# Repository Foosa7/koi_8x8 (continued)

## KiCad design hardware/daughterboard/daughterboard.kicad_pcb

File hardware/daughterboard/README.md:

# Daughterboard — 8-channel analog board

The analog front-end board for Koi 8×8. Eight of these plug into one
[motherboard](../motherboard/) over a PCIe-x4 card-edge connector, giving the
system 8 boards × 8 channels = 64 independent current sources with voltage
readback. Formerly codenamed `OuttaQontrol`/`OuttaControl`.

| Top | Bottom |
| --- | --- |
|  |  |

Same top view with an alpha background, for dropping onto slides or into the
paper's figures:

## What's on it

| Ref | Part | Function |
| --- | --- | --- |
| U0–U7 | XTR200 (WSON-10) | Precision current-source front end, one per channel |
| U20 | DAC80508Z (WQFN-16) | 16-bit, 8-channel DAC — sets the 8 channel currents |
| U11 | AD7193 (TSSOP-28) | 24-bit ΔΣ ADC — reads back the 8 channel voltages |
| U10 | REF5030 (SOIC-8) | 3.0 V precision reference, shared by the DAC and ADC on this board |
| U8 | SN74LV165A (TSSOP-16) | Parallel-load 8-bit shift register |
| U9 | AT21CS01 | 1-Wire EEPROM (board ID/config) — new in this revision |
| R19–R26 | 4.7 kΩ 0.1 % | Per-channel sense resistors |
| R1–R4, R9–R12, R17 / R5–R8, R13–R16 | 100 kΩ / 20 kΩ 0.1 % | 6:1 sense divider (top/bottom) — firmware reads the raw ADC-pin voltage and the host applies ×6 to get true heater voltage |
| J1 | Custom PCIe-x4 card-edge | Connector into the motherboard slot |

Full pricing and part numbers: [`../../master_bom.csv`](../../master_bom.csv).

## Files

| File | What it is |
| --- | --- |
| `daughterboard.kicad_pro` / `.kicad_sch` / `.kicad_pcb` | The KiCad project (current revision) |
| `Schematics/daughterboard.pdf` | Exported schematic |
| `bom/ibom.html` | Interactive HTML BOM (open in a browser) |
| `production/` | Fab outputs — gerbers, BOM, positions, netlist |
| `daughterboard*.png` | Board views above, regenerated with `kicad-cli pcb render` |
| `version 1/` | The prior board revision (pre-EEPROM), kept for reference, incl. its own PDN sim results |
| `padne_out_v3/`, `results_v3/` | Power-delivery-network (PDN) simulation outputs for this revision — current-density and IR-drop maps |

Photorealistic Cycles renders (`daughterboard_render*.png`) are produced by the
pipeline in [`../render/`](../render/) — not generated yet.

See **[`CLAUDE.md`](CLAUDE.md)** for the full development-facing breakdown of
these files, the netlist/revision history, and the padne PDN simulation
workflow in detail.

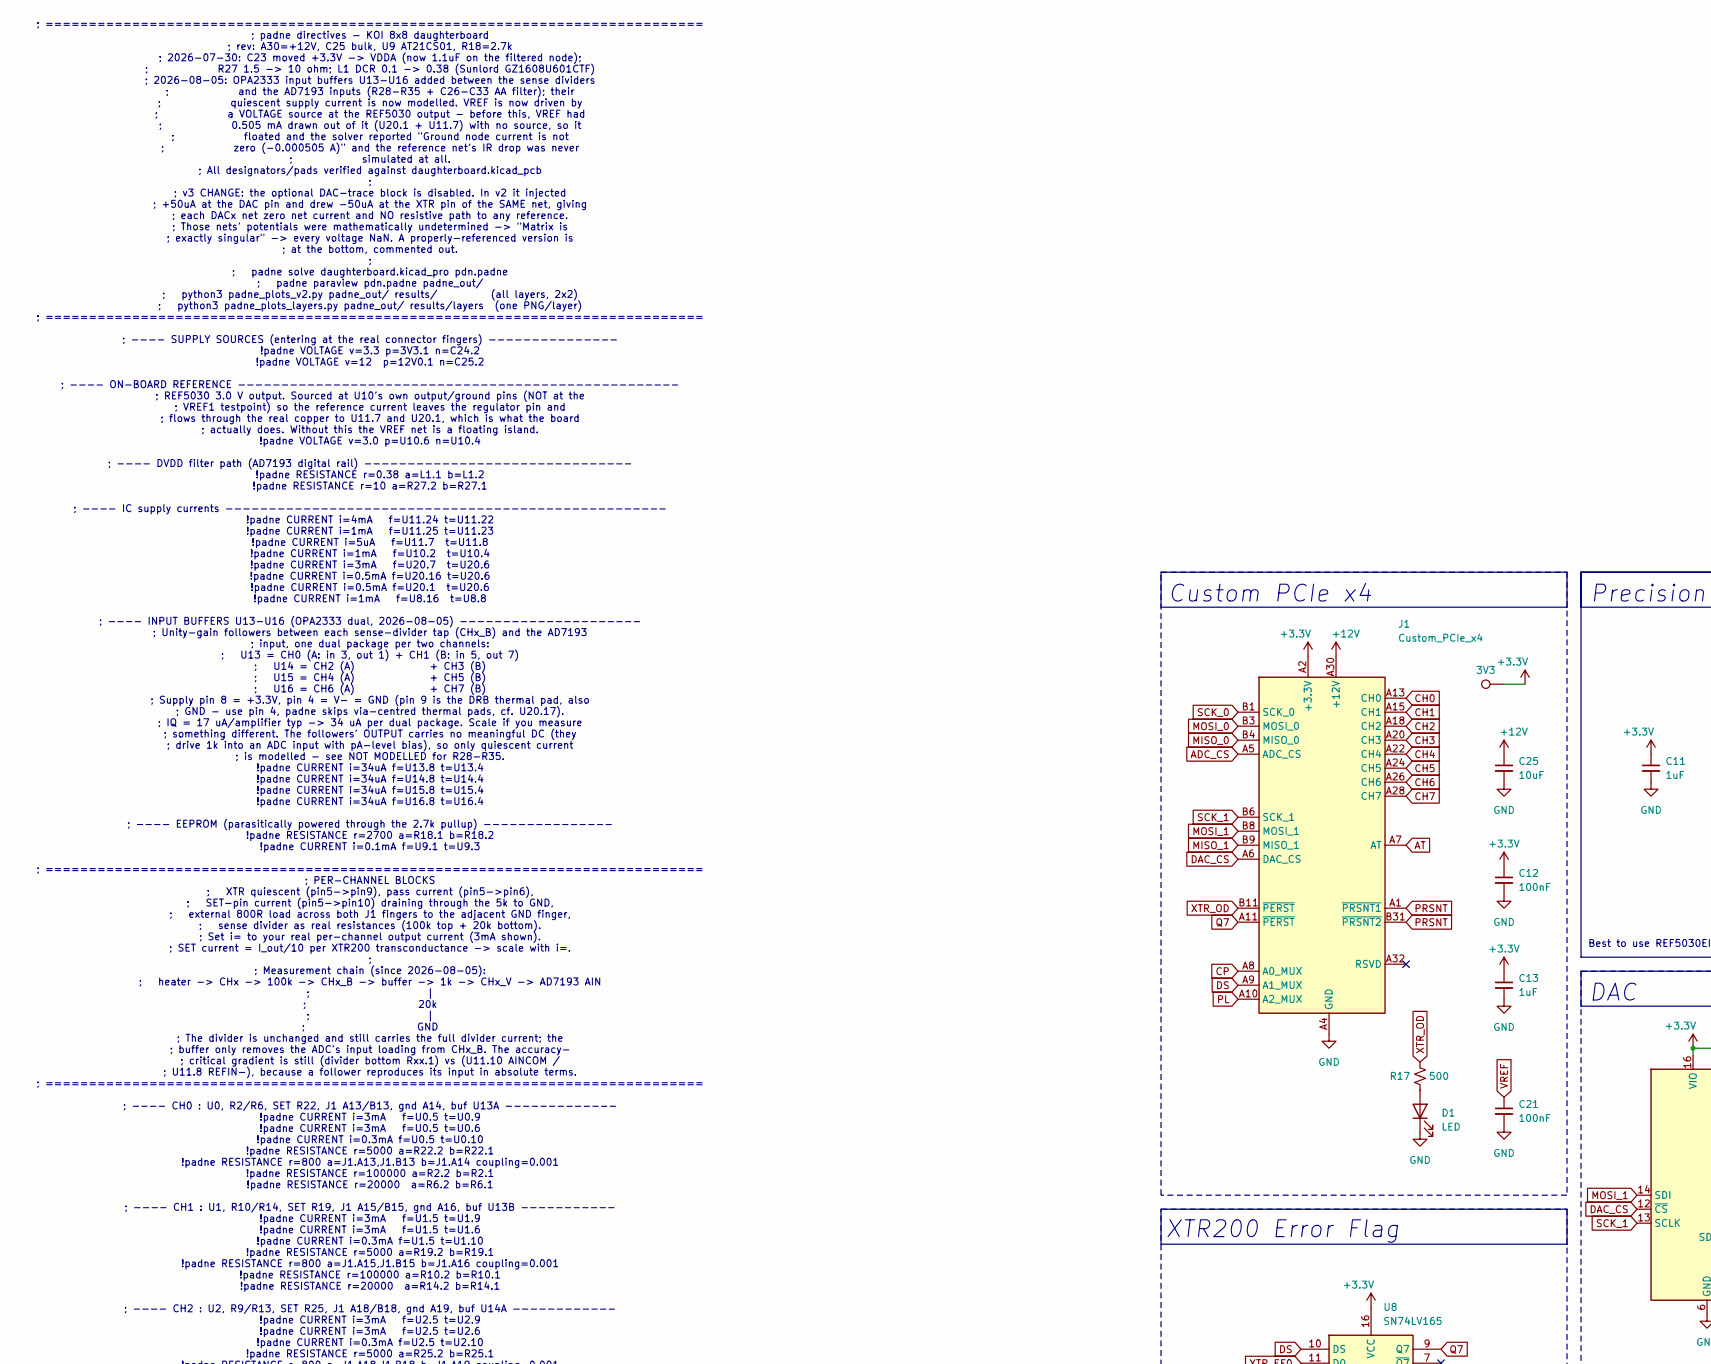
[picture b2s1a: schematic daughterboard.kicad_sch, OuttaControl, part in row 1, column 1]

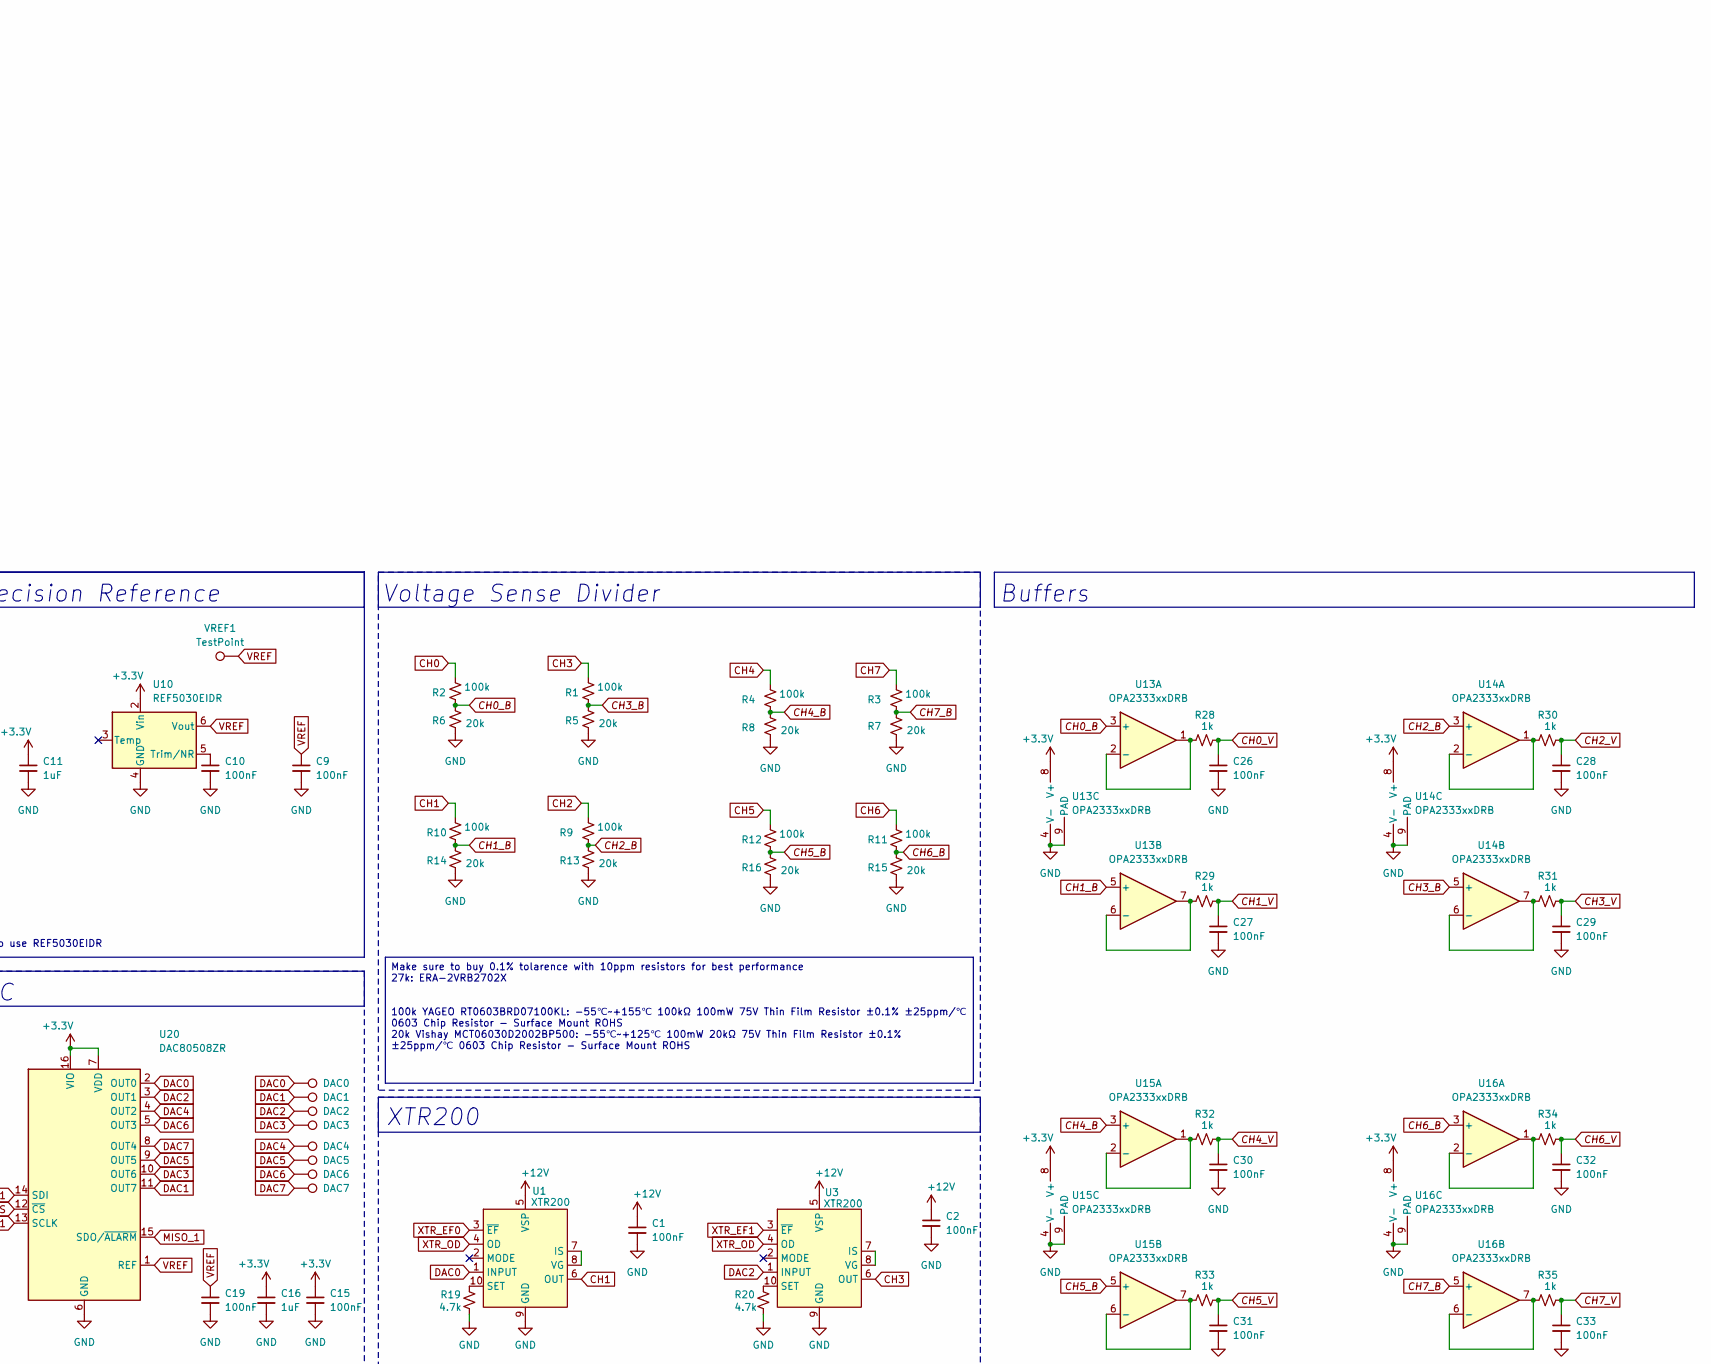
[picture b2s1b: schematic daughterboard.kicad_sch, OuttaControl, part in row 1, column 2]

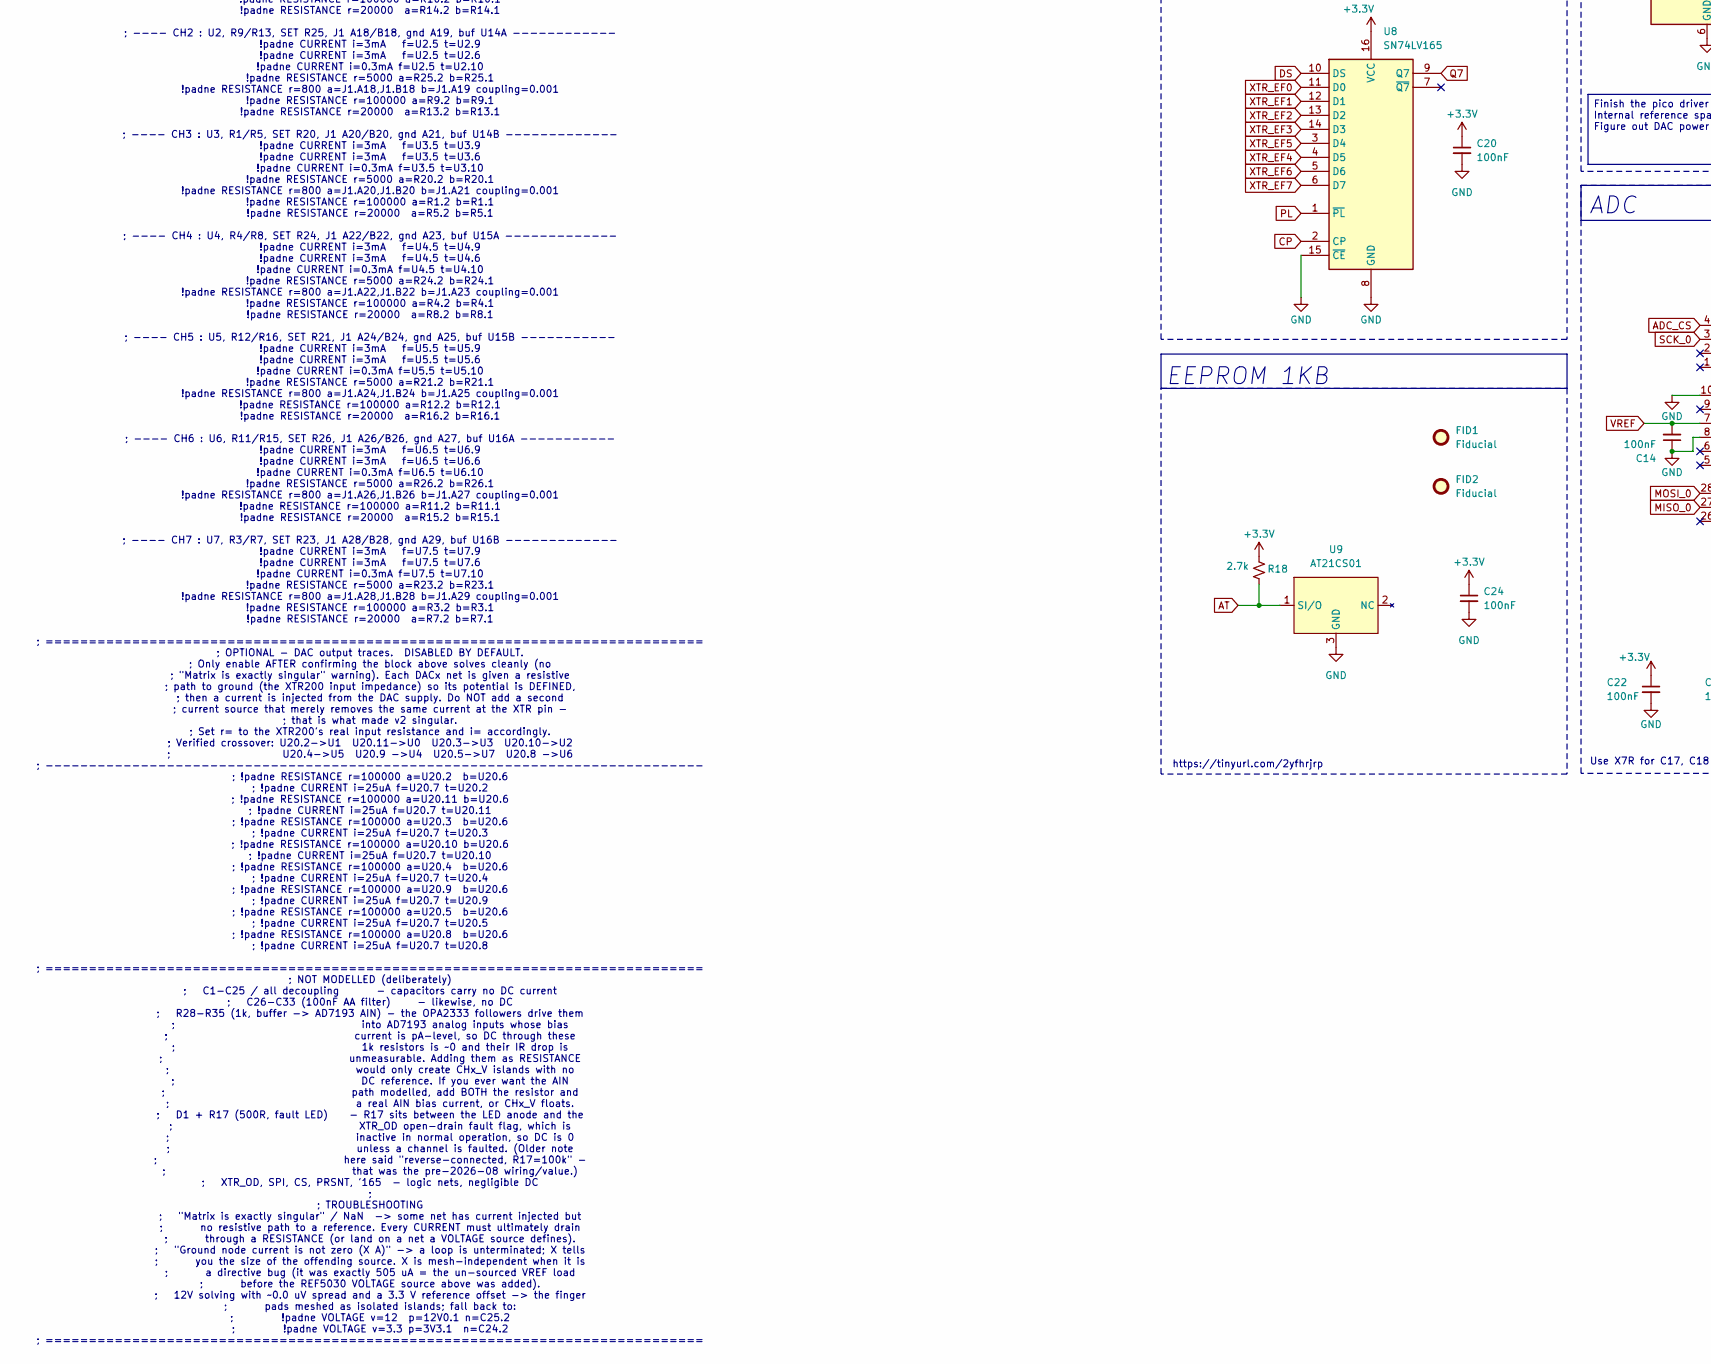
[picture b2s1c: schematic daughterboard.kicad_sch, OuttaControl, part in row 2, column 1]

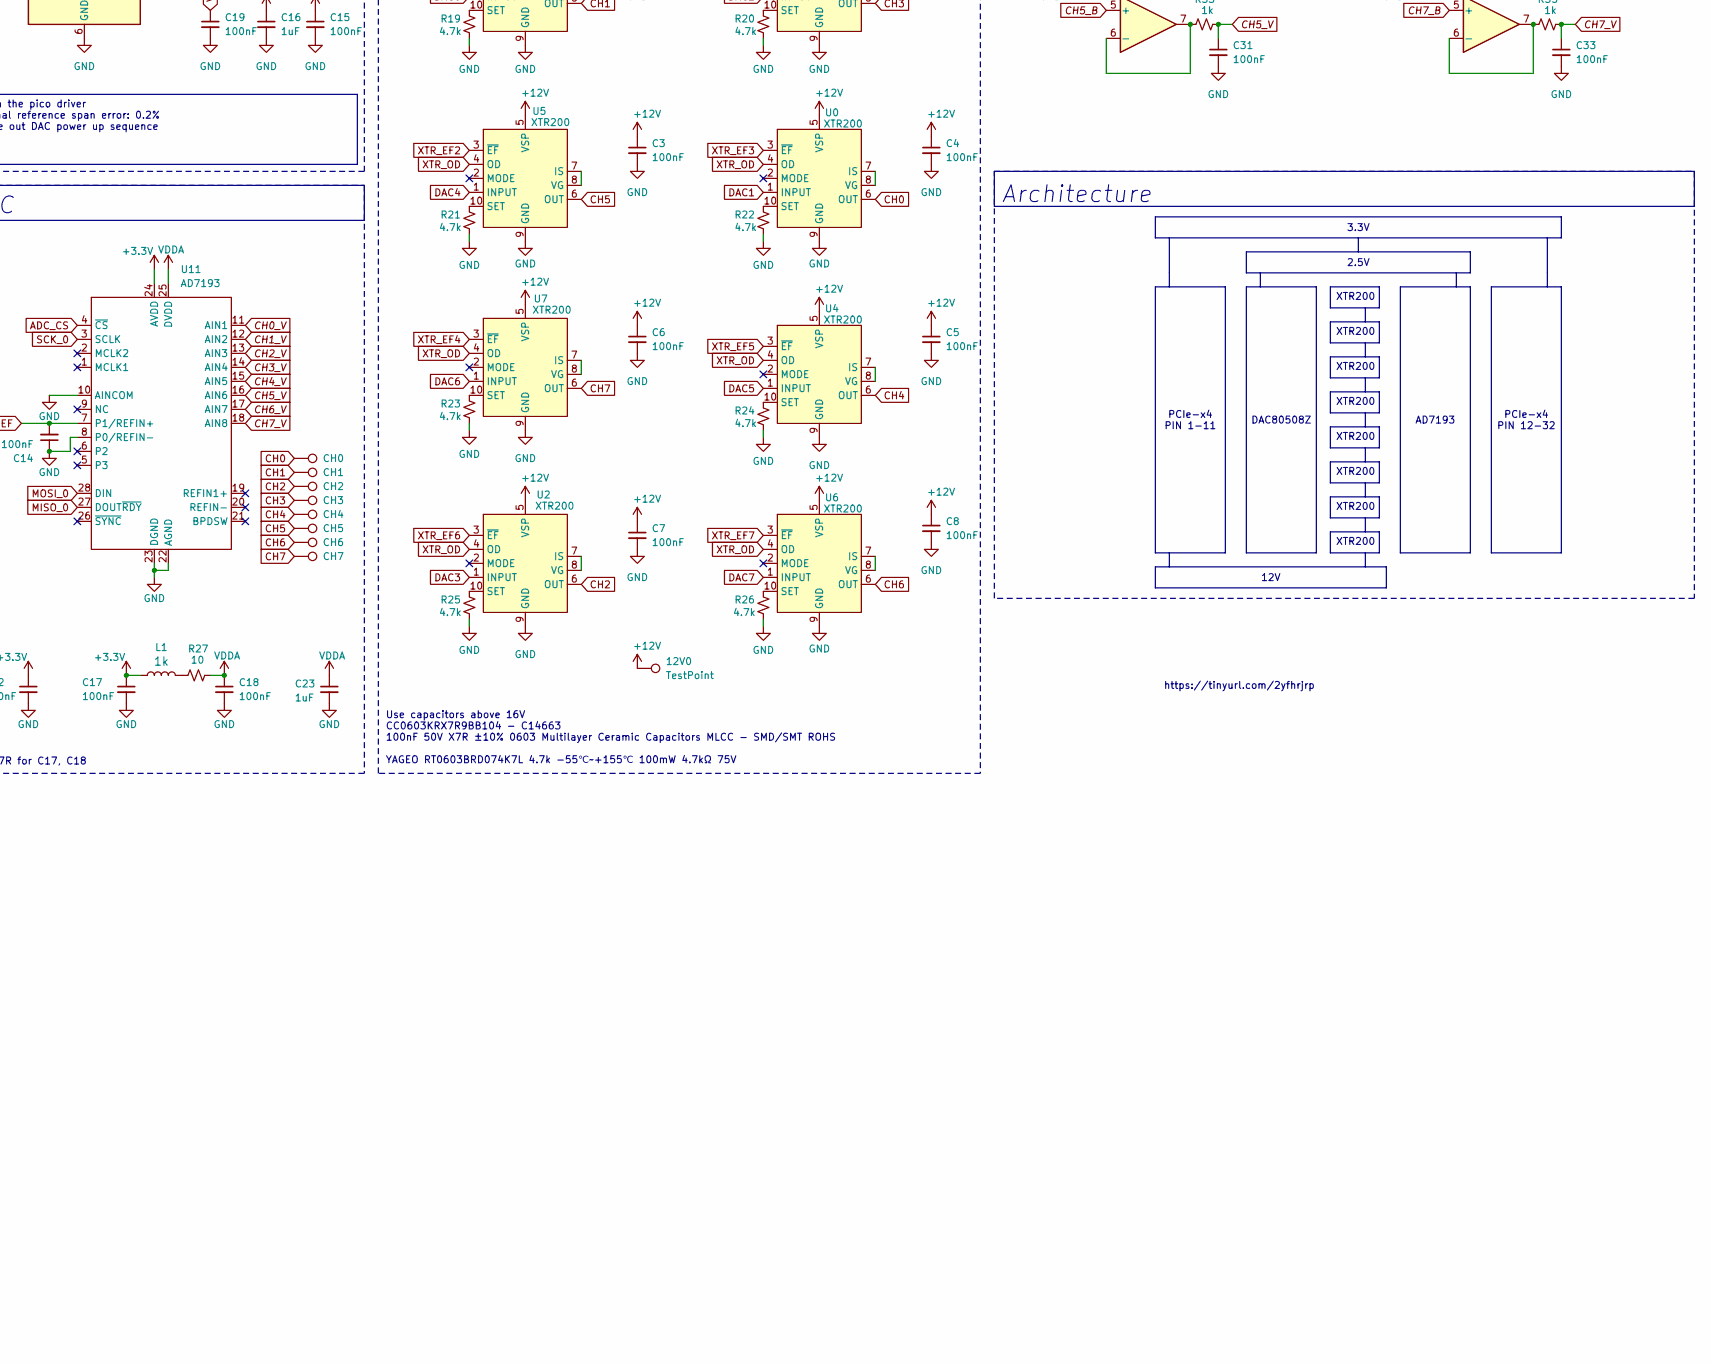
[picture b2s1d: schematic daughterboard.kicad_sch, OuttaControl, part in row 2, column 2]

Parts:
3V3: TestPoint_Pad_D1.0mm
12V0: TestPoint; TestPoint_Pad_D1.0mm
C1, C2, C3, C4, C5, C6, C7, C8, C9, C10, C12, C14, C15, C17, C18, C19, C20, C21, C22, C24, C26, C27, C28, C29, C30, C31, C32, C33: 100nF; C_0603_1608Metric; LCSC C14663
C11, C13, C16, C23: 1uF; C_0603_1608Metric; LCSC C15849
C25: 10uF; C_0603_1608Metric; LCSC C96446
CH0, CH1, CH2, CH3, CH4, CH5, CH6, CH7: TestPoint_Pad_D1.0mm
D1: LED; LED_0603_1608Metric; LCSC C125114
DAC0, DAC1, DAC2, DAC3, DAC4, DAC5, DAC6, DAC7: TestPoint_Pad_D1.0mm
FID1, FID2: Fiducial; Fiducial_1mm_Mask2mm
J1: Custom_PCIe_x4; Custom_BUS_PCIexpress_x4
L1: FerriteBead_0603_1.5A; L_0603_1608Metric; Part Number FCM1608KF-601T05; LCSC C133937
R1, R2, R3, R4, R9, R10, R11, R12: 100k; R_0603_1608Metric; LCSC C122538
R5, R6, R7, R8, R13, R14, R15, R16: 20k; R_0603_1608Metric; LCSC C154077
R17: 500; R_0603_1608Metric; LCSC C23179
R18: 2.7k; R_0603_1608Metric; LCSC C13167
R19, R20, R21, R22, R23, R24, R25, R26: 4.7k; R_0603_1608Metric; LCSC C513565
R27: 10; R_0603_1608Metric; LCSC C144117
R28, R29, R30, R31, R32, R33, R34, R35: 1k; R_0603_1608Metric; LCSC C22548
U0, U1, U2, U3, U4, U5, U6, U7: XTR200; WSON-10-1EP_2x3mm_P0.5mm_EP0.84x2.4mm; LCSC C52091642
U8: SN74LV165; TSSOP-16_4.4x5mm_P0.65mm; LCSC C201716
U9: AT21CS01; SOT-23; LCSC C616192
U10: REF5030EIDR; SOIC-8_3.9x4.9mm_P1.27mm
U11: AD7193; TSSOP-28-1EP_4.4x9.7mm_P0.65mm_EP3.05x7.56mm
U13, U14, U15, U16: OPA2333xxDRB; Texas_S-PVSON-N8; LCSC C2058573
U20: DAC80508ZR; WQFN-16-1EP_3x3mm_P0.5mm_EP1.6x1.6mm; LCSC C2679499
VREF1: TestPoint; TestPoint_Pad_D1.0mm

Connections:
+3.3V: 3V3.1 (1_1), C11.1, C12.1, C13.1, C15.1, C16.1, C17.1, C20.1, C22.1, C24.1, J1.A2 (+3.3V), L1.1, R18.1, U8.16 (VCC), U10.2 (Vin), U11.24 (AVDD), U13.8 (V+), U14.8 (V+), U15.8 (V+), U16.8 (V+), U20.7 (VDD), U20.16 (VIO)
+12V: 12V0.1 (1_1), C1.1, C2.1, C3.1, C4.1, C5.1, C6.1, C7.1, C8.1, C25.1, J1.A30 (+12V), U0.5 (VSP), U1.5 (VSP), U2.5 (VSP), U3.5 (VSP), U4.5 (VSP), U5.5 (VSP), U6.5 (VSP), U7.5 (VSP)
ADC_CS: J1.A5 (ADC_CS), U11.4 (~CS)
AT: J1.A7 (AT), R18.2, U9.1 (SI/O)
CH0: CH0.1 (1_1), J1.A13 (CH0), J1.B13 (CH0), R2.2, U0.6 (OUT)
CH0_B: R2.1, R6.2, U13.3 (+)
CH0_V: C26.1, R28.1, U11.11 (AIN1)
CH1: CH1.1 (1_1), J1.A15 (CH1), J1.B15 (CH1), R10.2, U1.6 (OUT)
CH1_B: R10.1, R14.2, U13.5 (+)
CH1_V: C27.1, R29.1, U11.12 (AIN2)
CH2: CH2.1 (1_1), J1.A18 (CH2), J1.B18 (CH2), R9.2, U2.6 (OUT)
CH2_B: R9.1, R13.2, U14.3 (+)
CH2_V: C28.1, R30.1, U11.13 (AIN3)
CH3: CH3.1 (1_1), J1.A20 (CH3), J1.B20 (CH3), R1.2, U3.6 (OUT)
CH3_B: R1.1, R5.2, U14.5 (+)
CH3_V: C29.1, R31.1, U11.14 (AIN4)
CH4: CH4.1 (1_1), J1.A22 (CH4), J1.B22 (CH4), R4.2, U4.6 (OUT)
CH4_B: R4.1, R8.2, U15.3 (+)
CH4_V: C30.1, R32.1, U11.15 (AIN5)
CH5: CH5.1 (1_1), J1.A24 (CH5), J1.B24 (CH5), R12.2, U5.6 (OUT)
CH5_B: R12.1, R16.2, U15.5 (+)
CH5_V: C31.1, R33.1, U11.16 (AIN6)
CH6: CH6.1 (1_1), J1.A26 (CH6), J1.B26 (CH6), R11.2, U6.6 (OUT)
CH6_B: R11.1, R15.2, U16.3 (+)
CH6_V: C32.1, R34.1, U11.17 (AIN7)
CH7: CH7.1 (1_1), J1.A28 (CH7), J1.B28 (CH7), R3.2, U7.6 (OUT)
CH7_B: R3.1, R7.2, U16.5 (+)
CH7_V: C33.1, R35.1, U11.18 (AIN8)
CP: J1.A8 (A0_MUX), U8.2 (CP)
DAC0: DAC0.1 (1_1), U1.1 (INPUT), U20.2 (OUT0)
DAC1: DAC1.1 (1_1), U0.1 (INPUT), U20.11 (OUT7)
DAC2: DAC2.1 (1_1), U3.1 (INPUT), U20.3 (OUT1)
DAC3: DAC3.1 (1_1), U2.1 (INPUT), U20.10 (OUT6)
DAC4: DAC4.1 (1_1), U5.1 (INPUT), U20.4 (OUT2)
DAC5: DAC5.1 (1_1), U4.1 (INPUT), U20.9 (OUT5)
DAC6: DAC6.1 (1_1), U7.1 (INPUT), U20.5 (OUT3)
DAC7: DAC7.1 (1_1), U6.1 (INPUT), U20.8 (OUT4)
DAC_CS: J1.A6 (DAC_CS), U20.12 (~CS)
DS: J1.A9 (A1_MUX), U8.10 (DS)
GND: C1.2, C2.2, C3.2, C4.2, C5.2, C6.2, C7.2, C8.2, C9.2, C10.2, C11.2, C12.2, C13.2, C14.1, C15.2, C16.2, C17.2, C18.2, C19.2, C20.2, C21.2, C22.2, C23.2, C24.2, C25.2, C26.2, C27.2, C28.2, C29.2, C30.2, C31.2, C32.2, C33.2, D1.1 (K), J1.A3 (GND), J1.A4 (GND), J1.A12 (GND), J1.A14 (CH0), J1.A16 (CH1), J1.A17 (GND), J1.A19 (CH2), J1.A21 (CH3), J1.A23 (CH4), J1.A25 (CH5), J1.A27 (CH6), J1.A29 (CH7), J1.A31 (GND), J1.B2 (GND), J1.B5 (GND), J1.B7 (GND), J1.B10 (GND), J1.B12 (GND), J1.B14 (CH0), J1.B16 (CH1), J1.B19 (CH2), J1.B21 (CH3), J1.B23 (CH4), J1.B25 (CH5), J1.B27 (CH6), J1.B29 (CH7), J1.B32 (GND), R5.1, R6.1, R7.1, R8.1, R13.1, R14.1, R15.1, R16.1, R19.1, R20.1, R21.1, R22.1, R23.1, R24.1, R25.1, R26.1, U0.9 (GND), U0.11 (PAD), U1.9 (GND), U1.11 (PAD), U2.9 (GND), U2.11 (PAD), U3.9 (GND), U3.11 (PAD), U4.9 (GND), U4.11 (PAD), U5.9 (GND), U5.11 (PAD), U6.9 (GND), U6.11 (PAD), U7.9 (GND), U7.11 (PAD), U8.8 (GND), U8.15 (~CE), U9.3 (GND), U10.4 (GND), U11.8 (P0/REFIN-), U11.10 (AINCOM), U11.22 (AGND), U11.23 (DGND), U11.29 (DGND), U13.4 (V-), U13.9 (PAD), U14.4 (V-), U14.9 (PAD), U15.4 (V-), U15.9 (PAD), U16.4 (V-), U16.9 (PAD), U20.6 (GND), U20.17 (Thermal)
MISO_0: J1.B4 (MISO_0), U11.27 (DOUT~RDY)
MISO_1: J1.B9 (MISO_1), U20.15 (SDO/~ALARM)
MOSI_0: J1.B3 (MOSI_0), U11.28 (DIN)
MOSI_1: J1.B8 (MOSI_1), U20.14 (SDI)
unnamed: D1.2 (A), R17.1
unnamed: L1.2, R27.2
unnamed: U0.7 (IS), U0.8 (VG)
unnamed: R22.2, U0.10 (SET)
unnamed: U1.7 (IS), U1.8 (VG)
unnamed: R19.2, U1.10 (SET)
unnamed: U2.7 (IS), U2.8 (VG)
unnamed: R25.2, U2.10 (SET)
unnamed: U3.7 (IS), U3.8 (VG)
unnamed: R20.2, U3.10 (SET)
unnamed: U4.7 (IS), U4.8 (VG)
unnamed: R24.2, U4.10 (SET)
unnamed: U5.7 (IS), U5.8 (VG)
unnamed: R21.2, U5.10 (SET)
unnamed: U6.7 (IS), U6.8 (VG)
unnamed: R26.2, U6.10 (SET)
unnamed: U7.7 (IS), U7.8 (VG)
unnamed: R23.2, U7.10 (SET)
unnamed: C10.1, U10.5 (Trim/NR)
unnamed: R28.2, U13.1, U13.2 (-)
unnamed: R29.2, U13.6 (-), U13.7
unnamed: R30.2, U14.1, U14.2 (-)
unnamed: R31.2, U14.6 (-), U14.7
unnamed: R32.2, U15.1, U15.2 (-)
unnamed: R33.2, U15.6 (-), U15.7
unnamed: R34.2, U16.1, U16.2 (-)
unnamed: R35.2, U16.6 (-), U16.7
PL: J1.A10 (A2_MUX), U8.1 (~PL)
PRSNT: J1.A1 (~PRSNT1), J1.B31 (~PRSNT2)
Q7: J1.A11 (~PERST), U8.9 (Q7)
SCK_0: J1.B1 (SCK_0), U11.3 (SCLK)
SCK_1: J1.B6 (SCK_1), U20.13 (SCLK)
VDDA: C18.1, C23.1, R27.1, U11.25 (DVDD)
VREF: C9.1, C14.2, C19.1, C21.1, U10.6 (Vout), U11.7 (P1/REFIN+), U20.1 (REF), VREF1.1 (1_1)
XTR_EF0: U1.3 (~EF), U8.11 (D0)
XTR_EF1: U3.3 (~EF), U8.12 (D1)
XTR_EF2: U5.3 (~EF), U8.13 (D2)
XTR_EF3: U0.3 (~EF), U8.14 (D3)
XTR_EF4: U7.3 (~EF), U8.4 (D5)
XTR_EF5: U4.3 (~EF), U8.3 (D4)
XTR_EF6: U2.3 (~EF), U8.5 (D6)
XTR_EF7: U6.3 (~EF), U8.6 (D7)
XTR_OD: J1.B11 (~PERST), R17.2, U0.4 (OD), U1.4 (OD), U2.4 (OD), U3.4 (OD), U4.4 (OD), U5.4 (OD), U6.4 (OD), U7.4 (OD)

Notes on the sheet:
Voltage Sense Divider
ADC
XTR200
Use X7R for C17, C18
; ============================================================================ ; padne directives - KOI 8x8 daughterboard ; rev: A30=+12V, C25 bulk, U9 AT21CS01, R18=2.7k ; 2026-07-30: C23 moved +3.3V -> VDDA (now 1.1uF on the filtered node); ; R27 1.5 -> 10 ohm; L1 DCR 0.1 -> 0.38 (Sunlord GZ1608U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
Best to use REF5030EIDR
https://tinyurl.com/2yfhrjrp
Use capacitors above 16V CC0603KRX7R9BB104 - C14663 100nF 50V X7R ±10% 0603 Multilayer Ceramic Capacitors MLCC - SMD/SMT ROHS YAGEO RT0603BRD074K7L 4.7k -55℃~+155℃ 100mW 4.7kΩ 75V
Buffers
EEPROM 1KB
XTR200 Error Flag
DAC
Architecture
Custom PCIe x4
Precision Reference
Finish the pico driver Internal reference span error: 0.2% Figure out DAC power up sequence
12V
DAC80508Z
2.5V
AD7193
Make sure to buy 0.1% tolarence with 10ppm resistors for best performance 27k: ERA-2VRB2702X 100k YAGEO RT0603BRD07100KL: -55℃~+155℃ 100kΩ 100mW 75V Thin Film Resistor ±0.1% ±25ppm/℃ 0603 Chip Resistor - Surface Mount ROHS 20k Vishay MCT06030D2002BP500: -55℃~+125℃ 100mW 20kΩ 75V Thin Film Resistor 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
3.3V
PCIe-x4 PIN 12-32
PCIe-x4 PIN 1-11

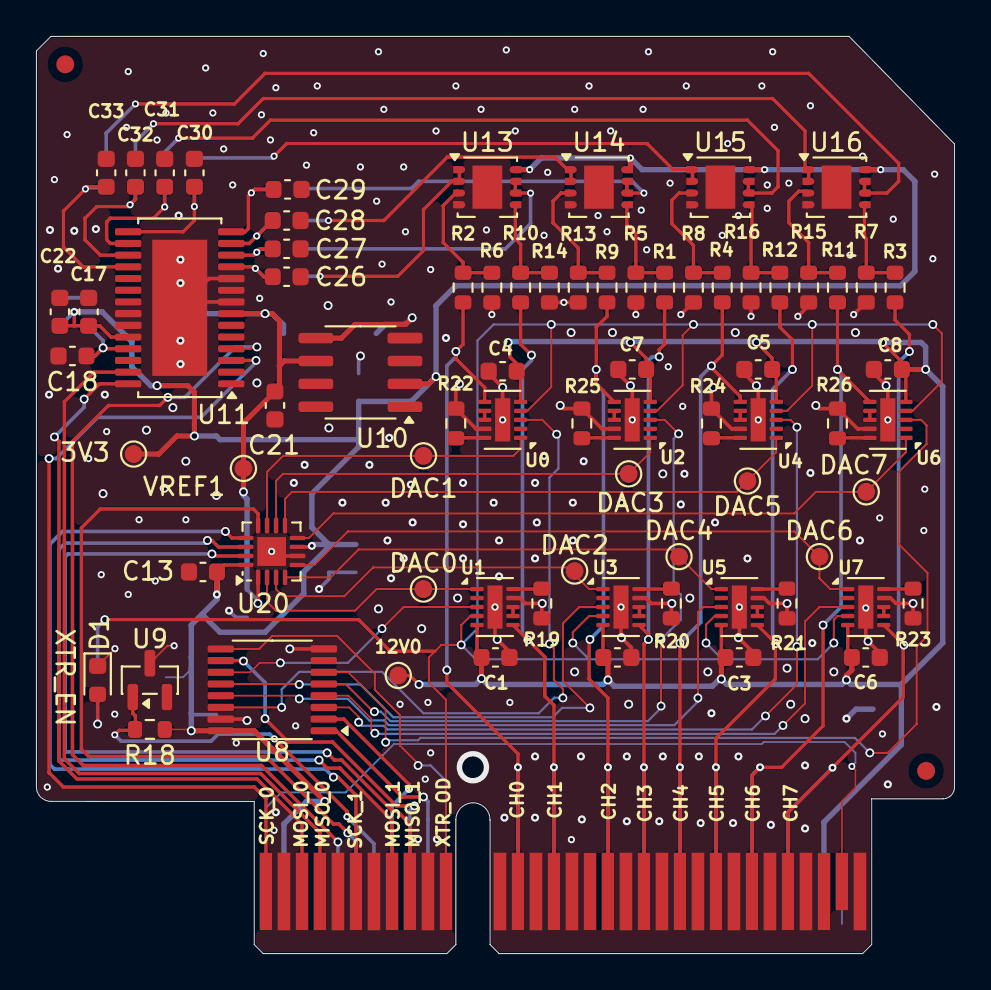
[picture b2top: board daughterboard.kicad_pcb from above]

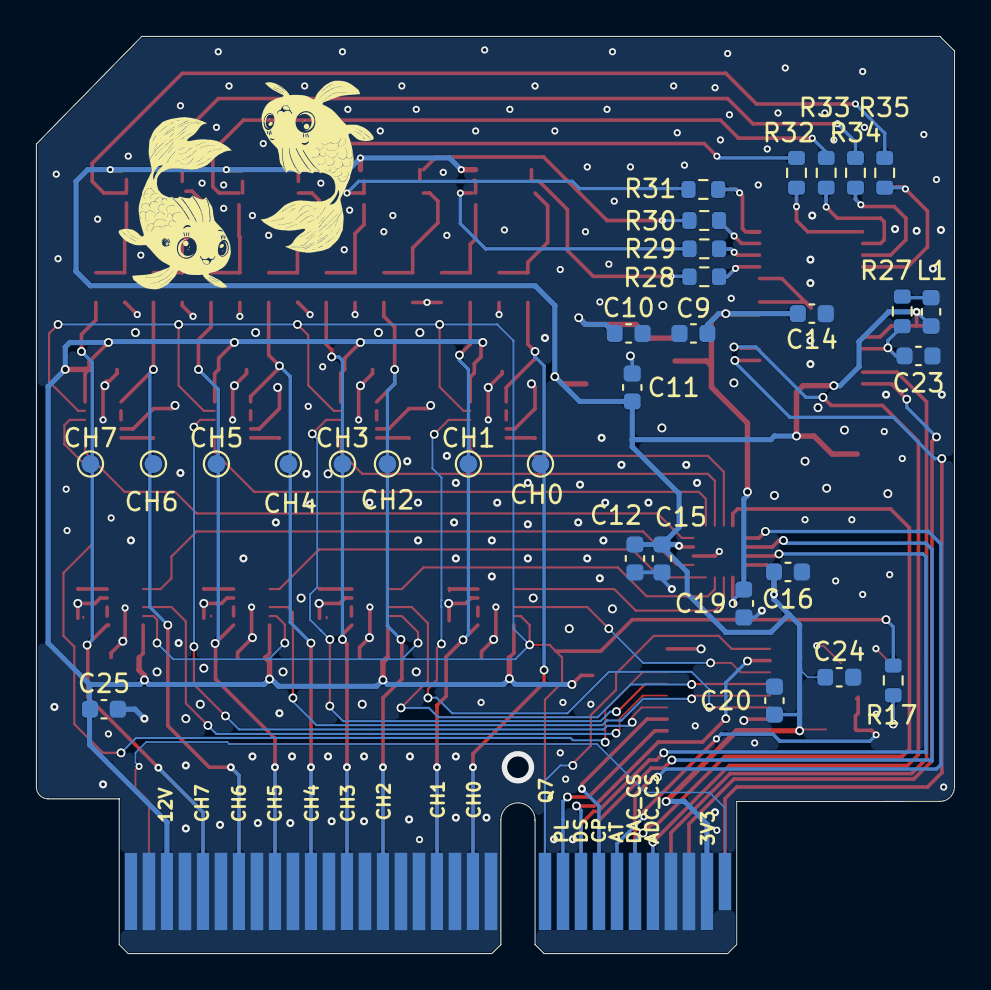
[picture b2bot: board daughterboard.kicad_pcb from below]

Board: 4 copper layers, 51.0 x 51.0 mm, 109 parts (31 on the bottom side), 87 nets.

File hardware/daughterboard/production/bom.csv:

Designator,Footprint,Quantity,Value,LCSC Part #
"12V0, VREF1",TestPoint_Pad_D1.0mm,2,TestPoint,
"C1, C10, C12, C14, C15, C17, C18, C19, C2, C20, C21, C22, C24, C26, C27, C28, C29, C3, C30, C31, C32, C33, C4, C5, C6, C7, C8, C9",0603,28,100nF,C14663
"C11, C13, C16, C23",0603,4,1uF,C15849
C25,0603,1,10uF,C96446
D1,0603,1,LED,C125114
L1,0603,1,FerriteBead_0603_1.5A,C133937
"R1, R10, R11, R12, R2, R3, R4, R9",0603,8,100k,C122538
"R13, R14, R15, R16, R5, R6, R7, R8",0603,8,20k,C154077
R17,0603,1,500,C23179
R18,0603,1,2.7k,C13167
"R19, R20, R21, R22, R23, R24, R25, R26",0603,8,4.7k,C513565
R27,0603,1,10,C144117
"R28, R29, R30, R31, R32, R33, R34, R35",0603,8,1k,C22548
"U0, U1, U2, U3, U4, U5, U6, U7",WSON-10-1EP_2x3mm_P0.5mm_EP0.84x2.4mm,8,XTR200,C52091642
U10,SOIC-8_3.9x4.9mm_P1.27mm,1,REF5030EIDR,
U11,TSSOP-28-1EP_4.4x9.7mm_P0.65mm_EP3.05x7.56mm,1,AD7193,
"U13, U14, U15, U16",Texas_S-PVSON-N8,4,OPA2333xxDRB,C2058573
U20,WQFN-16-1EP_3x3mm_P0.5mm_EP1.6x1.6mm,1,DAC80508ZR,C2679499
U8,TSSOP-16_4.4x5mm_P0.65mm,1,SN74LV165,C201716
U9,SOT-23,1,AT21CS01,C616192

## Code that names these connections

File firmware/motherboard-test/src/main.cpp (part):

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#define PIN_ADDR0     20
#define PIN_ADDR1     21
#define PIN_ADDR2     22
#define PIN_ADC_EN     5
#define PIN_DAC_EN     6
#define PIN_XTR_RCLK   7

// ── SN74LV165 XTR200 ERRORFLAG chain (bit-banged, dedicated pins) ──
#define PIN_ERR_CP    16   // shift clock (rising edge)
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#define CAL_OFFSET_DEFAULT  0.00f   // volts

// ── Buses + decoders ────────────────────────────────────
HC138 adcSelect(PIN_ADDR0, PIN_ADDR1, PIN_ADDR2, PIN_ADC_EN);
HC138 dacSelect(PIN_ADDR0, PIN_ADDR1, PIN_ADDR2, PIN_DAC_EN);

//                            MISO  MOSI  SCK
// Must match the wiring: the AD7193 DOUT lines land on GP4, so the ADC read
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
DAC80508     dac(&dacSelect, &dacSpi, NUM_BOARDS, VREF);
AD7193Driver adc(&adcSelect, &adcSpi, NUM_BOARDS);
XTR595       xtr(&adcSpi, PIN_XTR_RCLK);

// ── Runtime state ───────────────────────────────────────
bool     boardActive[NUM_BOARDS];
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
